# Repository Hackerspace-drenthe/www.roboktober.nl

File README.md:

# Roboktober Monorepo

Dit is de centrale repository voor Roboktober van Hackerspace Drenthe: de website en API, elektronica, robotfirmware, presentaties, 3D-printontwerpen en foto's.

Roboktober is een oktober-evenement rond combat robots, met focus op bouwen, leren en community.

## Status: editie 2026 afgerond

**Bevestigd door Rein op 5 november 2026:** Roboktober 2026 is afgerond en klaar. De website is al enkele maanden operationeel en stabiel. De elektronica v4 werkt en is akkoord.

Deze repository bewaart het resultaat: website, robotbouwinformatie, firmware, ontwerpen, presentaties en beeldmateriaal. Historische plannen, audits en revisies blijven beschikbaar, maar zijn geen open opleverlijst voor 2026. Ideeën voor uitbreiding horen bij eventuele volgende edities. Normaal beheer, back-ups en veiligheidscontroles blijven van toepassing; projectafronding is geen nieuwe verklaring dat iedere afzonderlijke test of ontwerpvariant is gevalideerd.

## Wallie: website, uitleg en oorspronkelijke code

**Wallies werk is een belangrijke basis en inspiratiebron voor de robotbesturing, het mini-robotchassis en de presentatie.** Bezoek zijn eigen website en GitHub voor de oorspronkelijke uitleg, projecten en actuele ontwikkelingen:

- **Website:** [wallieonline.nl](https://wallieonline.nl/)
- **Robotcontroller-uitleg:** [WORC Robot Controller (Nederlands)](https://wallieonline.nl/blogs/worc-robot-controller-nl.html)
- **GitHub-profiel en alle repositories:** [github.com/wallieonline](https://github.com/wallieonline)

### Repositories voor de besturing

| Repository van Wallie | Wat vind je daar? |
| --- | --- |
| [wallieonline/worc-robot-controller-esp32c3](https://github.com/wallieonline/worc-robot-controller-esp32c3) | Robotcontrollerfirmware voor de ESP32-C3 en DRV8833; bron voor de upstream referenties en codevoorbeelden in dit project. |
| [wallieonline/worc-remote-controller-esp32](https://github.com/wallieonline/worc-remote-controller-esp32) | ESP32-afstandsbediening: de zenderkant van de besturingsketen en bron voor de presentatievoorbeelden. |

De lokale Roboktober-firmware en eigen ontwerpen zijn niet hetzelfde als Wallies actuele upstream projecten. De bewaarde firmwarebron en herkomst staan onder [electronics/firmware/upstream](./electronics/firmware/upstream/). Raadpleeg de licentie en bronvermelding van het betreffende bestand bij gebruik of herpublicatie; deze repository verleent geen algemene rechten op Wallies werk.

## Projectdoelen

De doelen zijn uitgewerkt in het [projectplan](./docs/PLAN.md):

1. Mensen warm maken voor het event met teaser-content, planning en sfeer.
2. Deelnemers helpen bouwen met complete en praktische bouwinformatie.
3. Assets duurzaam beschikbaar houden, zoals BOM, STL, bouwdocs, blog en links.
4. Een herbruikbare basis neerzetten voor toekomstige Roboktober-edities.

## Context

- Eerste editie: 2026.
- Publieke domeinnaam: https://roboktober.nl.
- Website-taal: Nederlands.

## Repository-structuur

De repository combineert **robotbouw**, **software**, **presentaties** en **beeldmateriaal**. De belangrijkste mappen staan hieronder. Firmware is onderdeel van `electronics`; er is geen aparte firmwaremap in de root.

```text
.
├── electronics/                 Elektronica en robotfirmware
│   ├── components/             Onderdelen en selectiecriteria
│   ├── pin-definitions/        Pincontracten voor de modules
│   ├── wiring/                 Bedrading en bouwinstructies
│   ├── schema/                 Elektrische ontwerpkeuzes
│   ├── kicad/                  PCB-projecten en revisies
│   └── firmware/               Eigen firmware en upstream bronnen
├── 3dprinter/                  Chassis en 3D-printonderdelen
│   ├── Wallieonline+Mini+Robot+chassis/
│   └── reinsdesigns/           Eigen ontwerpen en varianten
├── presentaties/               Presentatiebronnen per editie en taal
├── fotos/                      Foto's en video per onderwerp
├── roboktober-api/             Website-backend en beheer
├── roboktober-frontend/        Publieke website
├── deploy/                    Server- en deploymentbestanden
└── docs/                      Plannen en verdiepende documentatie
```

Dit is een functioneel overzicht, geen volledige bestandslijst. Gebruik de links hieronder voor de inhoud en instructies per onderdeel.

### 1. Robotbouw: elektronica en firmware

[electronics](./electronics/README.md) bevat de informatie om de besturing van een antweight-robot op te bouwen: onderdelen, voedingskeuzes, pinnen, bedrading en PCB-ontwerpen. De controller draait rond een ESP32-C3 en een DRV8833-motordriver.

| Map | Inhoud en gebruik |
| --- | --- |
| [components](./electronics/components/) | Onderdelen/stuklijsten en selectiecriteria voor de elektronica. |
| [pin-definitions](./electronics/pin-definitions/) | Pincontracten en controlepunten: welke aansluiting hoort bij welke functie? |
| [wiring](./electronics/wiring/) | Bedradingsinstructies voor de bouw en het zoeken naar aansluitproblemen. |
| [schema](./electronics/schema/) | Elektrische ontwerpkeuzes en netspecificaties. |
| [kicad](./electronics/kicad/) | PCB-bronnen en revisies. Het [v4-project](./electronics/kicad/hsd-antweight-2s-v4/) is volgens de elektronica-handleiding het leidende ontwerp; oudere revisies zijn archiefreferenties. |
| [firmware](./electronics/firmware/) | Software die op de robotcontroller draait, met eigen firmware en bewaarde upstream bronnen. |

Binnen firmware vind je:

- [roboktober-controller-v2](./electronics/firmware/roboktober-controller-v2/README.md): de eigen controllerfirmware, inclusief hardwarecontract, zenderconfiguratie, motorbesturing, invoervalidatie, failsafe en compileerinstructies.
- [upstream](./electronics/firmware/upstream/): oorspronkelijke referentiecode met bijbehorende licentie, om herkomst en verschillen te kunnen volgen.

**Begin bij de elektronica-handleiding en controleer daarna het pincontract en de firmwareconfiguratie.** Een passend bestand of geslaagde compilatie is geen bewijs dat de fysieke robot veilig werkt. Test met de wielen vrij van de grond en controleer de uitschakeling bij verbindingsverlies.

### 2. Mechanica: chassis en 3D-printontwerpen

[3dprinter](./3dprinter/) bevat ontwerpbronnen en exports voor robotchassis en onderdelen. Een `.scad`-bestand is bewerkbare OpenSCAD-broncode; een `.stl` is een mesh voor onder andere de slicer. Er staan ook STEP-bestanden en afbeeldingen voor bepaalde ontwerpen.

- [Wallieonline+Mini+Robot+chassis](./3dprinter/Wallieonline+Mini+Robot+chassis/): Wallies mini-robotchassis en topplaat, met STL-bestanden en OpenSCAD-/STEP-varianten.
- [reinsdesigns](./3dprinter/reinsdesigns/): eigen ontwerpen en opeenvolgende varianten, waaronder Disc Spinner, Limulus, Passive Aggressive, Racer, Rhomboid en Mostly Harmless.
- [Print- en montagehandleiding](./3dprinter/README.md): schaaladvies en de beschreven passing van Wallies topplaat op de v4-PCB.

Versienummers in bestandsnamen maken ontwerpevolutie zichtbaar; ze betekenen niet automatisch dat elke variant is gebouwd of gevalideerd. Controleer vóór het printen de afmetingen, beschikbare onderdelen en de passing van jouw combinatie van chassis en elektronica.

### 3. Presentaties en uitleg

[presentaties](./presentaties/) bevat de presentatiebronnen per bijeenkomst en taal. Voor PHP Meetup Groningen op **5 november 2026** zijn er twee versies:

- [Nederlands](./presentaties/php-meetup-groningen-2026-11-05/slides/README.md)
- [Engels](./presentaties/php-meetup-groningen-2026-11-05-en/slides/README.md)

Elke versie heeft een `PLAN.md` en een `slides/`-map met de presentatie, stijlen, scripts, lokale afbeeldingen/video en speaker notes. De bijbehorende README beschrijft het openen en verpakken van de slides. De presentatie volgt de keten van joystick tot wiel en verbindt software, elektronica en chassisontwerp.

### 4. Foto's en video

[fotos](./fotos/) bewaart lokaal beeldmateriaal uit de bouw en het evenement:

| Map | Onderwerp |
| --- | --- |
| [controller](./fotos/controller/) | Controllers en besturing. |
| [mensenbezig](./fotos/mensenbezig/) | Deelnemers en bouwactiviteiten. |
| [robots](./fotos/robots/) | Gebouwde robots. |
| [video](./fotos/video/) | Videomateriaal. |

Presentaties hebben daarnaast hun eigen lokale slide-assets. Een bestand in deze repository betekent niet automatisch dat het vrij herpubliceerbaar is: behoud bronvermeldingen en controleer de toepasselijke rechten en toestemmingen.

### 5. Website, API en server

- [roboktober-api](./roboktober-api/README.md): Laravel-backend, API en Filament-beheer.
- [roboktober-frontend](./roboktober-frontend/README.md): Vue-frontend voor de publieke website.
- [deploy](./deploy/README.md): deploymentinstructies en configuratie voor Apache en systemd.

Deze onderdelen vormen het operationele webplatform, niet de robotfirmware. Architectuur, lokale ontwikkeling, Docker en deployment zijn uitgewerkt in [docs/SERVER.md](./docs/SERVER.md).

### 6. Plannen en projectdocumentatie

[docs](./docs/README.md) is de ingang naar de verdiepende documentatie:

- [PLAN.md](./docs/PLAN.md): functioneel en technisch masterplan.
- [PLAN-CHANGES.md](./docs/PLAN-CHANGES.md): aanvullingen en wijzigingen op het plan.
- [Architectuur](./docs/ARCHITECTUUR.md): platformarchitectuur.
- [Perspakket](./docs/pers/README.md): persinformatie en geselecteerd beeldmateriaal.
- [ADR's](./docs/adr/README.md) en [release notes](./docs/release-notes/README.md): vastgelegde keuzes en wijzigingshistoriek.

## Waar begin je?

| Je wilt… | Begin hier |
| --- | --- |
| Een robot bouwen of aansluiten | [Elektronica](./electronics/README.md), daarna [bedrading](./electronics/wiring/) en [firmware](./electronics/firmware/roboktober-controller-v2/README.md). |
| Een chassis kiezen, aanpassen of printen | [3D-printontwerpen](./3dprinter/) en de [printinstructies](./3dprinter/README.md). |
| De presentatie bekijken of voorbereiden | [Nederlandse](./presentaties/php-meetup-groningen-2026-11-05/slides/README.md) of [Engelse presentatie](./presentaties/php-meetup-groningen-2026-11-05-en/slides/README.md). |
| Beeldmateriaal zoeken | [Foto's en video](./fotos/); voor persgebruik het [perspakket](./docs/pers/README.md). |
| De website lokaal draaien of deployen | [Website en server](./docs/SERVER.md). |
| Scope, keuzes en projecthistoriek begrijpen | [Documentatie-index](./docs/README.md). |

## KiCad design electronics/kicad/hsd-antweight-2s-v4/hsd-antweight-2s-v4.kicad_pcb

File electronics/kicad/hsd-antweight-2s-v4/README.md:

# V4 print: module-based carrier board voor 1S LiPo default

Deze map bevat de v4-variant van de antweight-controllerprint. Het uitgangspunt is simpel:

- de PCB is de bron van waarheid
- de fysieke layout is gebaseerd op de bewezen v3-fix print
- de standaardopstelling is 1S LiPo
- de DRV8833 sleep/control pin zit op GPIO5
- 2S is alleen een expliciete optionele route, niet de default

## Projectstatus

Op 2026-11-05 heeft de gebruiker bevestigd dat de v4-elektronica werkt en
goedgekeurd is; het 2026-project is afgerond. Dit is geen nieuw testresultaat
of certificering en stelt niet vast dat elke optionele voedingsroute
afzonderlijk is getest.

## 1. Wat is de v4 in praktijk?

De v4 is geen volledig custom power-design. Het is een compacte carrier board voor bestaande modules:

- ESP32-C3 SuperMini
- DRV8833-breakout
- 1S LiPo charge/protection breakout
- motorconnectors
- testpoints en debug-headers

Het doel is om een praktische print te hebben die compact genoeg is voor een robot, zonder een ingewikkelde custom-voedingsarchitectuur te bouwen.

> Als een label, schema of document afwijkt van de PCB, dan geldt de PCB als de juiste referentie.

## 2. Standaardvoeding: 1S LiPo is de default

Voor deze robotbouw is de standaardconfiguratie:

- 1S LiPo batterij
- charge/protection breakout module
- output naar de PCB-power-rail
- ESP-logic en motor-power gescheiden houden

Dit betekent:

- de accu is een 1S-cel, ongeveer 3,7V tot 4,2V
- de ESP krijgt een veilige, gestabiliseerde 5V-rail via de module-route
- de motorstroom blijft apart van de ESP-logica
- de print is ontworpen voor de praktische standaardbouw, niet voor een complexe custom-power-variant

### 2.1 Waarom 1S als default?

- simpel
- compact
- veilig
- makkelijk te reproduceren
- het werkt het beste voor een kleine antweight-bouw met N20-motoren

### 2.2 Historische kostenindicatie: minimale 1S-kit

In de oorspronkelijke v4-planning werd een praktische richtprijs van ongeveer
EUR 25 voor een complete minimale 1S-kit per robot gehanteerd.

Dit is een historische inkoopindicatie, geen actuele offerte; de prijs kan
variëren door voorraad, leverancier, verzendkosten en batchgrootte.

### 2.3 Optionele 2S-route

Een 2S-configuratie kan als aparte route worden gebruikt, maar dat is bedoeld als alternatief en niet als standaardopstelling.

- 2S accu -> regulator -> ESP_5V_IN
- deze route moet expliciet worden gekozen en gecontroleerd
- meer vermogen, maar ook meer stroom, meer warmte en meer aandacht nodig

## 3. Belangrijkste elektrische afspraken

### DRV8833 sleep/control

GPIO5 is de sleep/control pin voor de DRV8833 in deze configuratie.

- niet zomaar vervangen door een willekeurige GPIO
- deze pin is onderdeel van de bedoeling van de print
- als je firmware of schema hier vanaf wijkt, dan is de PCB de bron van waarheid

### Power rails

Op deze print gelden deze afspraken:

- VBAT_RAW: ruwe batterijspanning
- VBAT_SW: geschakelde / gebruikelijke batterijrail
- ESP_5V_IN: 5V-ingang voor de ESP
- REG_5V_OUT: 5V-uitgang van een optionele regulator/route
- GND: massa

### Default path

De standaard route is:

- 1S LiPo charge/protection breakout -> VBAT_SW / ESP_5V_IN
- motor-power en ESP-power gescheiden houden
- 2S route aparte en optioneel

## 4. Eerste opstart: veilig en eenvoudig

### Stap 1: controleer de print

- controleer op beschadigde sporen of pads
- controleer de batterijconnector
- controleer de jumper/route voor je gekozen voeding

### Stap 2: kies je voeding

Gebruik deze eenvoudige regel:

- beginner / standaard: 1S-setup
- wedstrijd / speciale build: 2S optioneel via juiste regulator-route

Als je niet zeker bent, begin met de standaard 1S-opstelling.

### Stap 3: sluit de batterij aan

- zet de stroom uit voordat je iets aansluit
- sluit de batterij met juiste polariteit aan
- controleer GND en batterijpoles nogmaals

### Stap 4: sluit de motoren aan

- linker motor op linker connector
- rechter motor op rechter connector
- controleer of de pinning klopt

### Stap 5: zet de print aan

- controleer dat de ESP opstart
- controleer status en gedrag
- test zonder extra belasting eerst

## 5. Testen met USB-5V

Je kunt de ESP ook testen zonder de accu aan te sluiten door de print via USB-5V te voeden.

### Praktische regel

Gebruik altijd deze volgorde:

1. zet de batterij los
2. voer de print alleen via USB-5V
3. test de ESP en firmware
4. sluit daarna pas de accu weer aan voor een volledige batterijtest

### Belangrijk

Als USB-5V en accu tegelijk aanwezig zijn, kunnen beide voedingen op dezelfde print samenkomen. Dat is niet automatisch fataal, maar het kan leiden tot ongewenste backfeeding of onduidelijk gedrag.

Voor een veilige eerste test: batterij loskoppelen, dan USB-5V gebruiken, daarna pas opnieuw met accu testen.

## 6. Veilige bedradingsregels

- geen raw batterij direct op de 3.3V-rail van de ESP
- geen motor rechtstreeks op een ESP-pin
- alleen voeding op de daarvoor bestemde power-rails
- GND goed aansluiten tussen batterij, ESP en driver
- GPIO5 niet verwarren met een algemene vrije GPIO

## 7. Snelle technische samenvatting

- ESP-voeding: ESP_5V_IN
- standaard default: 1S LiPo
- optioneel alternatief: 2S via regulator route
- motorsturing: DRV8833
- sleep/control: GPIO5
- common ground: GND

## 8. Projectbestanden

- PCB: hsd-antweight-2s-v4.kicad_pcb
- Schema: hsd-antweight-2s-v4.kicad_sch
- Project: hsd-antweight-2s-v4.kicad_pro
- renders: renders/

## 9. Belangrijkste opmerking

Deze print is de werkelijke bron van waarheid. De v4 is een compacte
carrier-board-variant op basis van de v3-fix-layout, met 1S LiPo als standaard
en GPIO5 als DRV8833 sleep/control line. De oorspronkelijke beschrijving noemt
de v3-fix-layout bewezen; dit document voegt daar geen nieuwe fysieke
testresultaten aan toe.

De eerder vastgelegde DRC-controle van de PCB rapporteerde 0 violations en
0 unconnected items. Dit is het bestaande resultaat, geen nieuwe DRC-run.

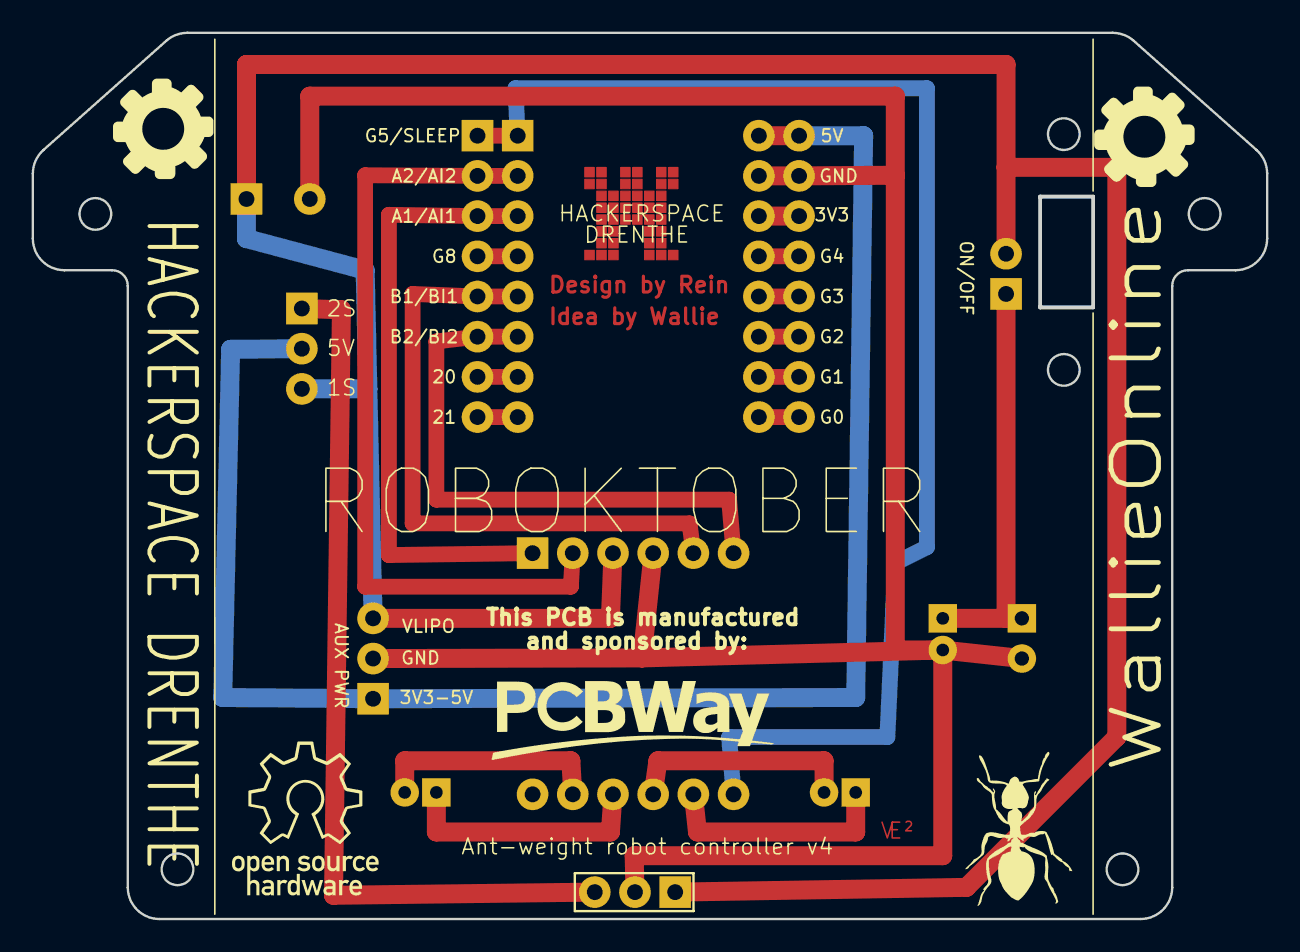
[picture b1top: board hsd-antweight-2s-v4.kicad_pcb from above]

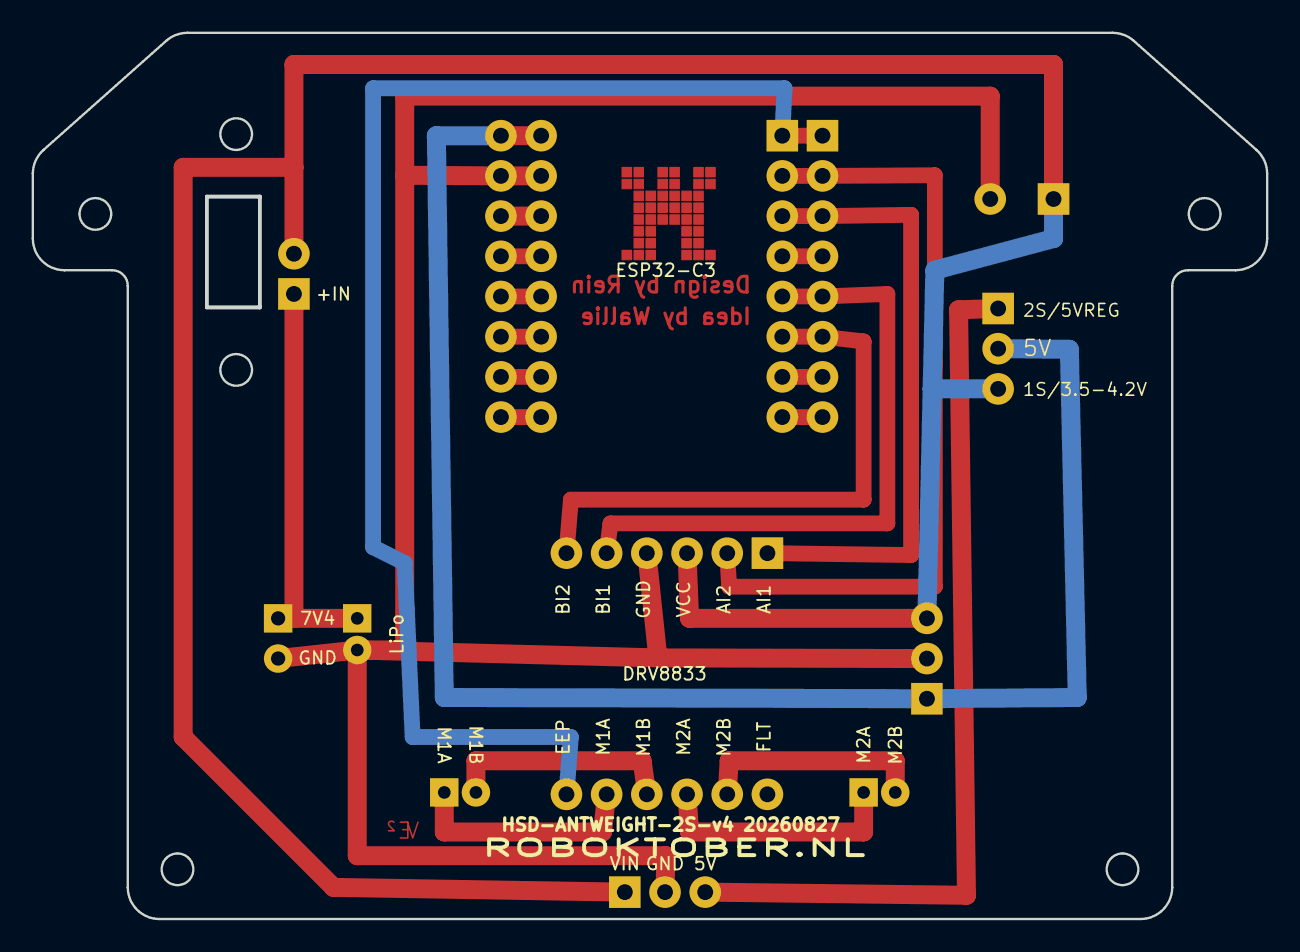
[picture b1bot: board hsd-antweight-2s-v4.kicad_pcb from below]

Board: 2 copper layers, 78.0 x 56.0 mm, 11 parts (10 on the bottom side), 14 nets.

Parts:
C1_C2: DRIVER CAPS; CAPS_DRIVER
J4: BATTERY; JST_PH_BATTERY
J4_ALT: BATTERY_ALT_2P_2.54; PinHeader_1x02_P2.54mm_Vertical
J5: MOTOR LEFT; JST_PH_MOTOR
J6: MOTOR RIGHT; JST_PH_MOTOR
J10: 5V(3.7-5V) GND VLIPO; ACCESSORY_POWER_1X03_UNPOPULATED
JP1: ESP 5V SEL: REG-ESP; ACCESSORY_POWER_1X03_UNPOPULATED
SW1: SW EXT VBAT_RAW/VBAT_SW; SWITCH_EXT_1X02
U1: ESP32-C3 SUPERMINI; ESP32_C3_SUPERMINI
U2: DRV8833; DRV8833_MACHINED_SOCKET_VERIFY
U3: EXT REG LOGIC VIN GND VOUT; REGULATOR_EXT_1X03

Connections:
AIN1_GPIO7: U1.3, U2.1
AIN2_GPIO6: U1.2, U2.3
BIN1_GPIO9: U1.5, U2.9
BIN2_GPIO10: U1.6, U2.11
ESP_5V_IN: J10.1, JP1.2, U1.16
GND: C1_C2.2, J4.2, J4_ALT.2, J10.2, U1.15, U2.7, U3.2
GPIO5: U1.1, U2.12
M1A: J5.1, U2.10
M1B: J5.2, U2.8
M2A: J6.1, U2.6
M2B: J6.2, U2.4
REG_5V_OUT: JP1.1, U3.3
VBAT_RAW: J4.1, J4_ALT.1, SW1.1
VBAT_SW: C1_C2.1, J10.3, JP1.3, SW1.2, U2.5, U3.1

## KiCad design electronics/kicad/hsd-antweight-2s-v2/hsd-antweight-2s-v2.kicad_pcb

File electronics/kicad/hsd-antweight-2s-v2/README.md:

# KiCad antweight controller v2 - hsd-antweight-2s-v2

This KiCad 9 project is the current 2S-oriented board variant with
externalized power interfaces.

Current board silk details:

- logo area: `HACKERSPACE` above `DRENTHE`
- J10 pad 3 raw rail silk: `VLIPO` (electrically `VBAT_SW`)

Power-mode placement update (component-only, routing deferred):

- Added `JP1` (`ESP PWR SEL: REG-3V3-1S`) near `U3`.
- `JP1` maps: `1=REG_3V3_2S`, `2=ESP_3V3`, `3=VBAT_SW`.
- 2S mode: place `U3`, shunt `JP1` pins `1-2`.
- 1S mode: do not place `U3` (DNP), shunt `JP1` pins `2-3`.
- Motor driver path still uses `VBAT_SW` directly in both modes.
- This revision intentionally focuses on component placement only; routing will be redone later.

## Status

The schematic is documented and the PCB is now proto-ready for
PCBWay 2-layer fabrication.

This folder diverges from the archived legacy board layout by externalizing
the power path:

- `SW1` is a 2-pin external switch header (`VBAT_RAW` <-> `VBAT_SW`).
- Bypass mode uses a 2-pin shunt directly on `SW1`.
- `U3` is a 3-pin external regulator header
  (`VIN`, `GND`, `VOUT=3V3`).

Use this revision for prototype fabrication only.
It is not yet a locked mass-production release.

## Validation

```bash
kicad-cli sch erc --severity-error \
  electronics/kicad/hsd-antweight-2s-v2/hsd-antweight-2s-v2.kicad_sch
kicad-cli sch export netlist \
  electronics/kicad/hsd-antweight-2s-v2/hsd-antweight-2s-v2.sch
kicad-cli pcb drc \
  electronics/kicad/hsd-antweight-2s-v2/hsd-antweight-2s-v2.kicad_pcb \
  --severity-all
```

Latest validation snapshot (2026-08-12):

- ERC errors: 0 (`--severity-error` gate passes)
- DRC violations: 0
- Unconnected pads: 0
- Footprint errors: 0
- Full ERC warning report still contains expected legacy wiring warnings.

Before manufacturing review:

- convert the schematic fully to native KiCad format;
- replace all `*_VERIFY` footprints with production footprints;
- rerun ERC and DRC after every electrical/layout change;
- inspect antenna clearance and high-current routes.

## PCBWay proto package

Generated package root:

- `production/pcbway/`

Upload-ready archive:

- `production/pcbway/hsd-antweight-2s-v2-pcbway-proto-package-2026-08-12.zip`

Contents:

- `gerbers/`: copper, mask, silkscreen and edge cuts Gerbers
- `drill/`: PTH/NPTH drill files, maps and drill report
- `hsd-antweight-2s-v2-pos.csv`: placement file
- `hsd-antweight-2s-v2-bom.csv`: BOM export
- `hsd-antweight-2s-v2.net`: KiCad netlist export

## 3D render (current revision)

Render images are stored in `renders/`.
All renders in this folder are PCB-only (no external connectors, modules or capacitors).

Primary preview (top overview, PCB-only):

Generated artifacts (6 views):

- Top:
  - `renders/pcbway-bare-top-1-overview.png`
  - `renders/pcbway-bare-top-2-angle-left.png`
  - `renders/pcbway-bare-top-3-angle-right.png`
- Bottom:
  - `renders/pcbway-bare-bottom-1-overview.png`
  - `renders/pcbway-bare-bottom-2-angle-left.png`
  - `renders/pcbway-bare-bottom-3-angle-right.png`

Render command:

Settings below are tuned so the complete PCB (including holes, pads,
traces and vias) stays visible in frame.

```bash
PCB="electronics/kicad/hsd-antweight-2s-v2/hsd-antweight-2s-v2.kicad_pcb"
TMP="electronics/kicad/hsd-antweight-2s-v2/hsd-antweight-2s-v2-no-3dmodels.tmp.kicad_pcb"

perl -ne '
sub balance { my ($s)=@_; my $o=()=$s=~/\(/g; my $c=()=$s=~/\)/g; return $o-$c; }
if (!$skip && /\(model\s+/) { $skip=1; $depth=balance($_); next; }
if ($skip) { $depth += balance($_); if ($depth <= 0) { $skip=0; } next; }
print;
' "$PCB" > "$TMP"

kicad-cli pcb render \
  --width 3200 \
  --height 2400 \
  --background transparent \
  --quality high \
  --zoom 1.00 \
  --rotate "0,0,0" \
  --side top \
  --output \
  electronics/kicad/hsd-antweight-2s-v2/renders/pcbway-bare-top-1-overview.png \
  "$TMP"

kicad-cli pcb render \
  --width 3200 \
  --height 2400 \
  --background transparent \
  --quality high \
  --perspective \
  --zoom 1.04 \
  --rotate "-20,0,18" \
  --side top \
  --output \
  electronics/kicad/hsd-antweight-2s-v2/renders/pcbway-bare-top-2-angle-left.png \
  "$TMP"

kicad-cli pcb render \
  --width 3200 \
  --height 2400 \
  --background transparent \
  --quality high \
  --perspective \
  --zoom 1.04 \
  --rotate "20,0,-18" \
  --side top \
  --output \
  electronics/kicad/hsd-antweight-2s-v2/renders/pcbway-bare-top-3-angle-right.png \
  "$TMP"

rm -f "$TMP"
```

Render bottom views (PCB-only):

```bash
PCB="electronics/kicad/hsd-antweight-2s-v2/hsd-antweight-2s-v2.kicad_pcb"
TMP="electronics/kicad/hsd-antweight-2s-v2/hsd-antweight-2s-v2-no-3dmodels.tmp.kicad_pcb"

perl -ne '
sub balance { my ($s)=@_; my $o=()=$s=~/\(/g; my $c=()=$s=~/\)/g; return $o-$c; }
if (!$skip && /\(model\s+/) { $skip=1; $depth=balance($_); next; }
if ($skip) { $depth += balance($_); if ($depth <= 0) { $skip=0; } next; }
print;
' "$PCB" > "$TMP"

kicad-cli pcb render \
  --width 3200 \
  --height 2400 \
  --background transparent \
  --quality high \
  --zoom 1.00 \
  --rotate "0,0,0" \
  --side bottom \
  --output \
  electronics/kicad/hsd-antweight-2s-v2/renders/pcbway-bare-bottom-1-overview.png \
  "$TMP"

kicad-cli pcb render \
  --width 3200 \
  --height 2400 \
  --background transparent \
  --quality high \
  --perspective \
  --zoom 1.04 \
  --rotate "-20,0,18" \
  --side bottom \
  --output \
  electronics/kicad/hsd-antweight-2s-v2/renders/pcbway-bare-bottom-2-angle-left.png \
  "$TMP"

kicad-cli pcb render \
  --width 3200 \
  --height 2400 \
  --background transparent \
  --quality high \
  --perspective \
  --zoom 1.04 \
  --rotate "20,0,-18" \
  --side bottom \
  --output \
  electronics/kicad/hsd-antweight-2s-v2/renders/pcbway-bare-bottom-3-angle-right.png \
  "$TMP"

rm -f "$TMP"
```

## Release checklist

- [ ] `*_VERIFY` footprints replaced by production footprints.
- [ ] Mounting-hole implementation and coordinates verified.
- [ ] Current ratings validated for switch and connectors.
- [x] ERC and DRC rerun and reports archived.
- [ ] Final visual review completed.

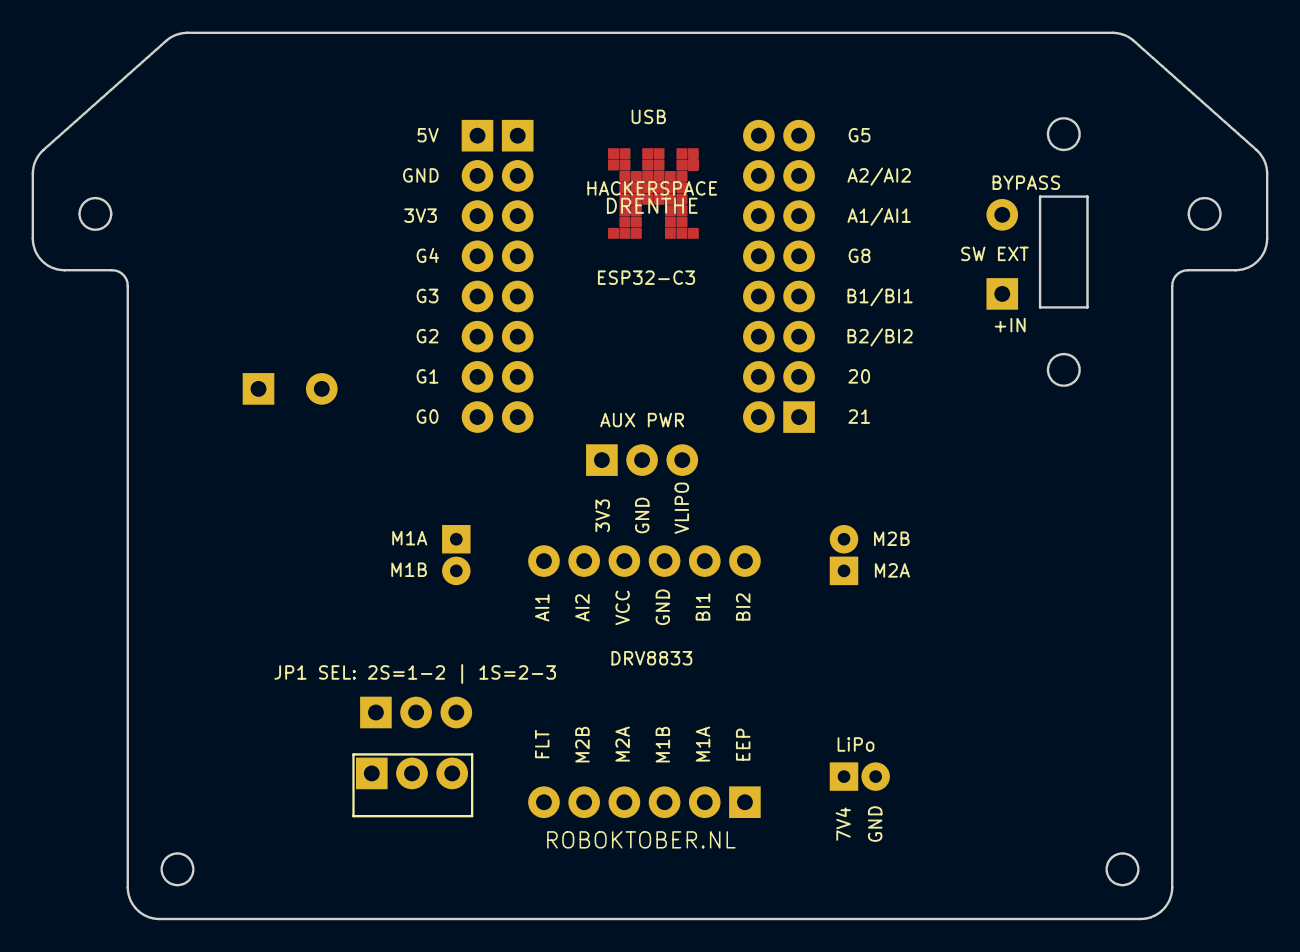
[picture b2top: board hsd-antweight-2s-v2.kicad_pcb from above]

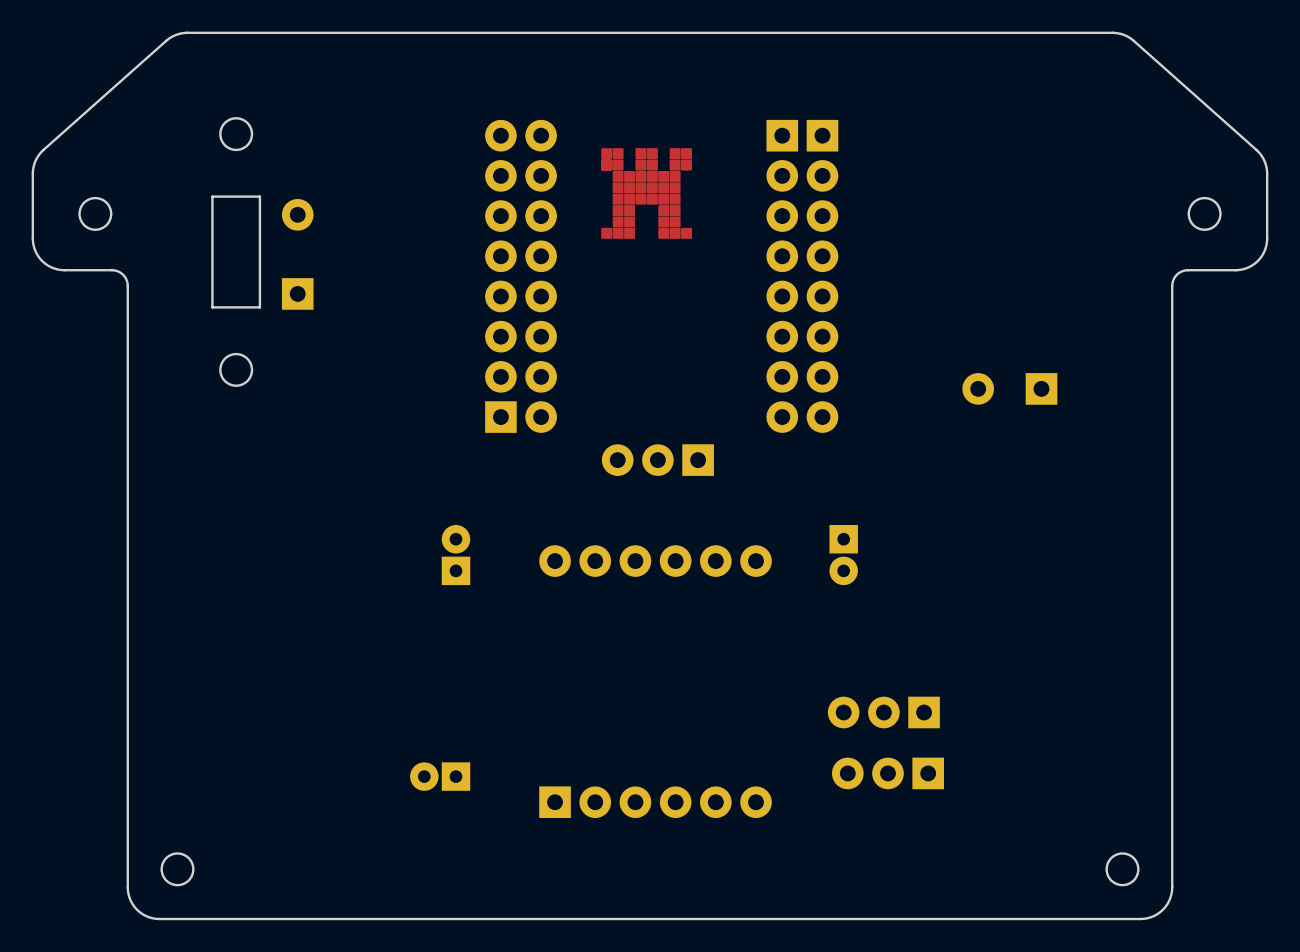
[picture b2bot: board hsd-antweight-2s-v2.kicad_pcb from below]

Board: 2 copper layers, 78.0 x 56.0 mm, 12 parts (11 on the bottom side), 23 nets, no tracks yet.

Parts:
C1_C2: DRIVER CAPS; CAPS_DRIVER
J4: BATTERY; JST_PH_BATTERY
J5: MOTOR LEFT; JST_PH_MOTOR
J6: MOTOR RIGHT; JST_PH_MOTOR
J8: ESP32 LEFT ALL PINS; ESP32_LEFT_ALL_PINS_BREAKOUT_1X08_UNPOPULATED
J9: ESP32 RIGHT SIGNALS; ESP32_RIGHT_SIGNAL_BREAKOUT_1X08_UNPOPULATED
J10: 3V3 GND VLIPO; ACCESSORY_POWER_1X03_UNPOPULATED
JP1: ESP PWR SEL: REG-3V3-1S; ACCESSORY_POWER_1X03_UNPOPULATED
SW1: SW EXT VBAT_RAW/VBAT_SW; SWITCH_EXT_1X02
U1: ESP32-C3 SUPERMINI; ESP32_C3_SUPERMINI
U2: DRV8833; DRV8833_MACHINED_SOCKET_VERIFY
U3: EXT REG LOGIC VIN GND VOUT; REGULATOR_EXT_1X03

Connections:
3V3: J8.3, J10.1, JP1.2, U1.3
5V_NC: J8.1, U1.1
AIN1_GPIO7: J9.3, U1.11, U2.11
AIN2_GPIO6: J9.2, U1.10, U2.9
BIN1_GPIO9: J9.5, U1.13, U2.3
BIN2_GPIO10: J9.6, U1.14, U2.1
GND: C1_C2.2, J4.2, J8.2, J10.2, U1.2, U2.2, U2.5, U3.2
GPIO0_SPARE: J8.8, U1.8
GPIO1_SPARE: J8.7, U1.7
GPIO2_SPARE: J8.6, U1.6
GPIO3_SPARE: J8.5, U1.5
GPIO4_SPARE: J8.4, U1.4
GPIO5_SPARE: J9.1, U1.9
GPIO8_LED_EXPANSION: J9.4, U1.12
GPIO20_SPARE: J9.7, U1.15
GPIO21_SPARE: J9.8, U1.16
M1A: J5.1, U2.4
M1B: J5.2, U2.6
M2A: J6.1, U2.8
M2B: J6.2, U2.10
REG_3V3_2S: JP1.1, U3.3
VBAT_RAW: J4.1, SW1.1
VBAT_SW: C1_C2.1, J10.3, JP1.3, SW1.2, U2.7, U3.1

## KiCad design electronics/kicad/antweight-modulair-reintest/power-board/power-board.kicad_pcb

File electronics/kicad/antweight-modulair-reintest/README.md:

# Antweight modulair reintest

Dit ontwerp splitst de huidige controller op in twee stapelbare boards:

- `power-board/`: onderste board, met alleen power-conversie en power-distributie.
- `cpu-board/`: middelste board, met ESP32-C3, DRV8833, motorconnectoren en addon-header.

Een optionele derde board kan later als experiment/addon bovenop de CPU-board komen.

## Board split

CPU board verantwoordelijkheden:
- ESP32-C3 module/sockets
- DRV8833 driver
- motorconnectoren
- lokale driver-ontkoppeling
- stack-header naar power board
- addon-header voor spare GPIO en logic power
- logische netnamen voor motorbesturing

Power board verantwoordelijkheden:
- 2S LiPo ingang
- hoofdschakelaar
- buck 6V voor motoren
- buck 3.5V voor CPU-board
- stack-header omhoog naar CPU/DRV-board
- optionele aux power header

## Belangrijke nets

- `VBAT_2S_RAW`: ruwe 2S LiPo
- `VBAT_2S_SW`: geschakelde 2S LiPo
- `VMOTOR_6V`: gereguleerde motorvoeding
- `VCPU_3V5`: gereguleerde CPU-voeding
- `GND`
- `AIN1_GPIO7`, `AIN2_GPIO6`, `BIN1_GPIO9`, `BIN2_GPIO10`
- `M1A`, `M1B`, `M2A`, `M2B`
- `GPIO8_LED_EXPANSION`, `GPIO5_SPARE`

## Stack order

1. `power-board` onderaan
2. `cpu-board` in het midden
3. optionele addon/experiment board bovenop de CPU-board

De stack-header tussen power-board en CPU-board draagt alleen voedingsrails. Daardoor kan de power-board in theorie door een andere variant worden vervangen, bijvoorbeeld een 1S power-board, zonder DRV8833 of CPU-board te wisselen.

## Opmerking

De CPU-rail is hier expliciet als `VCPU_3V5` vastgelegd omdat dat gevraagd is. Controleer vóór hardwarebouw of de gekozen ESP32-C3 module direct 3.5V op zijn voedingspin mag hebben. Als dat niet kan, zet deze rail terug naar 3.3V in zowel schema als layout.

## Files

- `cpu-board/cpu-board.sch`: legacy schema bron voor CPU board
- `cpu-board/cpu-board.net`: geëxporteerde netlist
- `cpu-board/cpu-board.kicad_pcb`: eerste PCB met ESP32/DRV/motor-footprints
- `power-board/power-board.sch`: legacy schema bron voor power board
- `power-board/power-board.net`: geëxporteerde netlist
- `power-board/power-board.kicad_pcb`: eerste PCB met alleen power-footprints
- `stack-header-pinout.md`: interconnect pinout tussen beide boards

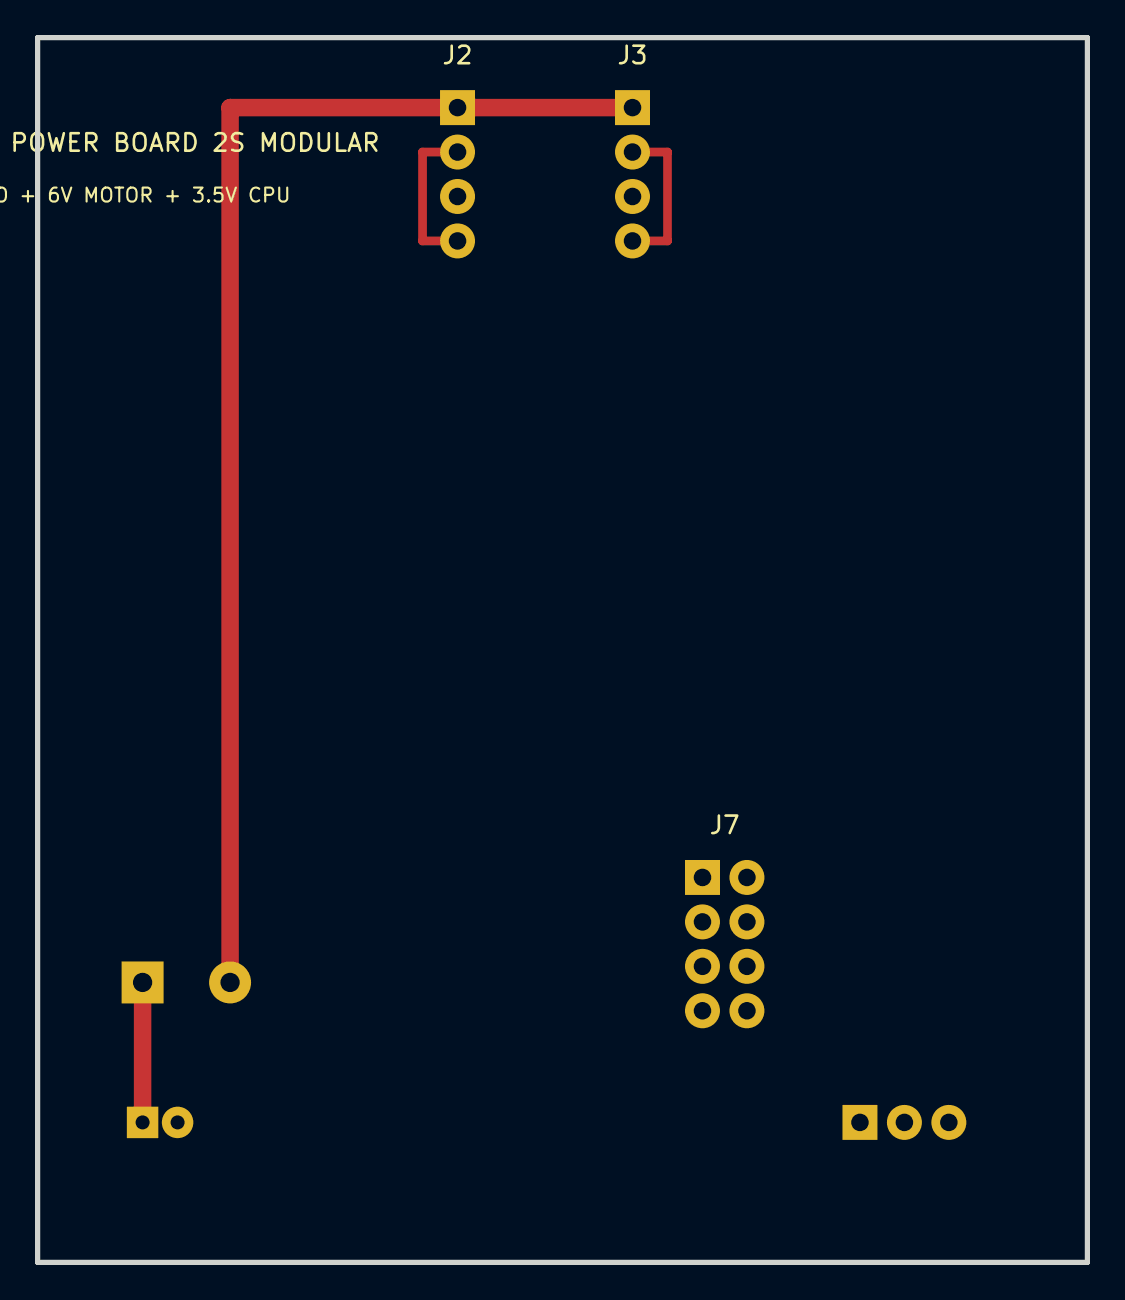
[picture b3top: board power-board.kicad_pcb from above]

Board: 2 copper layers, 60.0 x 70.0 mm, 6 parts (0 on the bottom side), 5 nets.

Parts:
J1: BATTERY_2S; JST_PH_BATTERY
J2: BUCK_6V_MOTOR; BUCK_HEADER_1X04
J3: BUCK_3V5_CPU; BUCK_HEADER_1X04
J7: STACK_TO_CPU_DRV; STACK_HEADER_2X04
J8: AUX_POWER; ACCESSORY_POWER_1X03_UNPOPULATED
SW1: MAIN_POWER; SWITCH_VERIFY

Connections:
GND: J1.2, J2.2, J2.4, J3.2, J3.4, J7.2, J7.4, J7.6, J7.8, J8.2
VBAT_2S_RAW: J1.1, SW1.1
VBAT_2S_SW: J2.1, J3.1, SW1.2
VCPU_3V5: J3.3, J7.1, J7.5, J8.1
VMOTOR_6V: J2.3, J7.3, J7.7, J8.3

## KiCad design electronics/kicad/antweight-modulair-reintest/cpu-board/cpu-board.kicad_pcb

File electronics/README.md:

# Roboktober electronics resources

Deze map bevat de gedeelde elektronica-informatie voor de Roboktober
antweight-builds.

## Inhoud

- `components/`: stuklijst en selectiecriteria voor onderdelen.
- `firmware/`: upstream referenties en de gereviewde Roboktober-firmware.
- `pin-definitions/`: logisch pincontract en controlepunten voor modules.
- `wiring/`: bedradingsinstructies voor bouw en foutzoeken.
- `schema/`: elektrische ontwerpkeuzes en netspecificatie.
- `kicad/antweight-controller-v2/`: historische legacy KiCad-projectmap
  (gearchiveerd).
- `kicad/hsd-antweight-2s-v4/`: leidend ontwerp voor de huidige
  ESP32-C3 controller revisie.
- `kicad/hsd-antweight-2s-v3-fix/`: historische tussenrevisie (archief).

Het leidende actieve ontwerp in deze repository is nu:

- v4 PCB: `kicad/hsd-antweight-2s-v4/`
- v4 power rule: minimale 1S setup is de standaard; 2S via regulator is optioneel
- v4 design notes: `docs/WALLIE-DESIGN-ISSUES.md`
- historische inkoopindicatie complete 1S-kit: ongeveer EUR 25 per robot

## Projectstatus

Op 2026-11-05 heeft de gebruiker bevestigd dat de v4-elektronica werkt en
goedgekeurd is; het 2026-project is afgerond. Dit is een brede
gebruikersbevestiging, geen nieuw testresultaat, certificering of verklaring
dat elke optionele voedingsconfiguratie afzonderlijk is getest.

De PCB in `kicad/hsd-antweight-2s-v4/` is de bron van waarheid voor het actuele ontwerp.
Legacy 3.3V-only en oudere 2S-documenten blijven alleen als archiefreferentie
bestaan voor vergelijking; ze zijn niet meer leidend voor bouw-, validatie- of
release-werk.

Publicatiestatus:

- De actieve v4-elektronica is door de gebruiker goedgekeurd zoals hierboven
  beschreven; er staat geen 2026 go/no-go- of prototypebesluit meer open.
- Die goedkeuring is geen certificering of bewijs van massaproductiegeschiktheid.
- Eerdere projectnotities beschreven de v4-print als proto-ready voor
  proefseries en hielden massaproductie tegen totdat footprints en thermische
  validatie definitief waren. Dat is een historische statusnotitie, geen
  openstaand projectbesluit; de huidige gebruikersbevestiging beweert niet dat
  die voorwaarden later zijn afgerond of dat massaproductie is vrijgegeven.
- De eerder genoemde circa EUR 25 per complete 1S-kit is een historische
  inkoopindicatie, geen actuele offerte.

## Reference design

Het leidende actieve ontwerp is de v4 revisie in `kicad/hsd-antweight-2s-v4/`.

Belangrijkste actuele regels:

- ESP32-C3 SuperMini voedt via `ESP_5V_IN`, niet via een legacy 3.3V-only rail;
- de module maakt intern 3.3V zelf; geen raw batterij op de ESP 3.3V pin;
- standaard route: minimale 1S setup via charge/protection breakout op de v4;
- optionele route: `2S -> 5V-regelaar -> ESP_5V_IN`;
- `VIN -> VOUT` bypass naar de ESP 3.3V rail blijft verboden;
- de v4 PCB en schematic zijn de bron van waarheid, niet de legacy 2S docs.

De oudere 2S/3.3V-only documenten in deze map blijven alleen als historische referentie
bestaan en mogen niet meer als actieve power-contract gelden.

Zie `docs/WALLIE-DESIGN-ISSUES.md` voor de definitieve design rules en
`kicad/hsd-antweight-2s-v4/README.md` voor de actuele PCB mapping.

## KiCad

Ontwerpstatus:

- v4 is het leidende ontwerp voor nieuwe hardware en validatie.
- De PCB en het schema in `kicad/hsd-antweight-2s-v4/` zijn de source-of-truth.
- Legacy ontwerpen in `kicad/hsd-antweight-2s-pcb/` en oudere mappen zijn archief.

Open `kicad/hsd-antweight-2s-v4/hsd-antweight-2s-v4.kicad_pro` met KiCad 9 of nieuwer.

Controleer bij een nieuwe revisie of onafhankelijke herhaling de actuele
power-path aan de hand van de PCB en het pincontract.

Voer voor een nieuwe revisie of onafhankelijke release-validatie minimaal uit:

```bash
kicad-cli sch erc --severity-error \
  kicad/hsd-antweight-2s-v4/hsd-antweight-2s-v4.kicad_sch
kicad-cli pcb drc kicad/hsd-antweight-2s-v4/hsd-antweight-2s-v4.kicad_pcb
```

Het ontwerp is geen gecertificeerd product. De bevestiging van de gebruiker
hierboven verandert dat niet. Test bij een nieuwe bouw eerst met een
stroombegrensde voeding en zonder gemonteerde motoren.

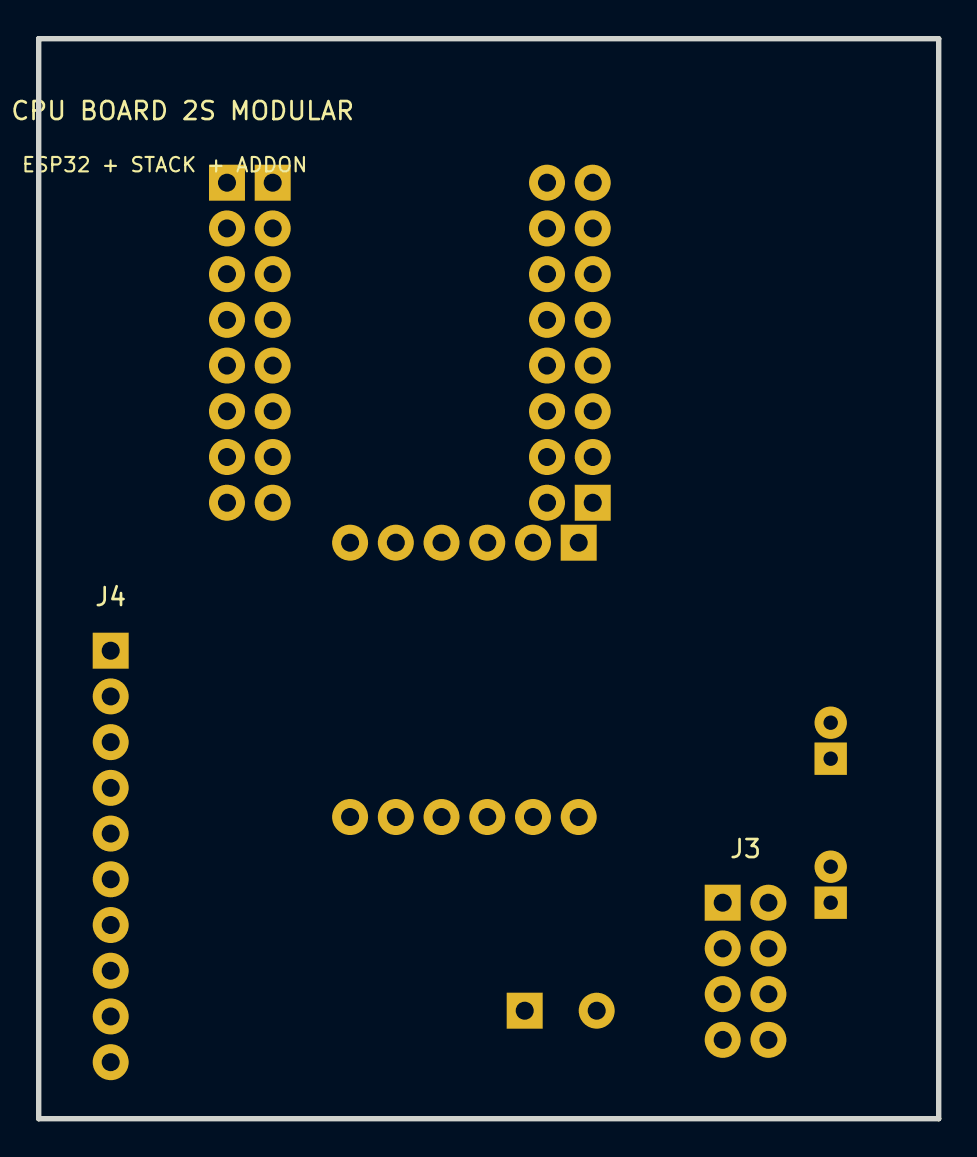
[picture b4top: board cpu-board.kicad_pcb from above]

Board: 2 copper layers, 50.0 x 60.0 mm, 9 parts (0 on the bottom side), 21 nets, no tracks yet.

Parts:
C1_C2: DRIVER CAPS; CAPS_DRIVER
J1: ESP32-C3_LEFT; ESP32_LEFT_ALL_PINS_BREAKOUT_1X08_UNPOPULATED
J2: ESP32-C3_RIGHT; ESP32_RIGHT_SIGNAL_BREAKOUT_1X08_UNPOPULATED
J3: STACK_TO_POWER; STACK_HEADER_2X04
J4: ADDON_HEADER; ADDON_HEADER_1X10
J5: MOTOR_LEFT; JST_PH_MOTOR
J6: MOTOR_RIGHT; JST_PH_MOTOR
U1: ESP32-C3 SUPERMINI; ESP32_C3_MACHINED_SOCKET_VERIFY
U2: DRV8833_BREAKOUT; DRV8833_MACHINED_SOCKET_VERIFY

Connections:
5V_NC: J1.1, U1.1
AIN1_GPIO7: J2.6, U1.14, U2.11
AIN2_GPIO6: J2.7, U1.15, U2.9
BIN1_GPIO9: J2.4, U1.12, U2.3
BIN2_GPIO10: J2.3, U1.11, U2.1
GND: C1_C2.2, J1.2, J3.2, J3.4, J3.6, J3.8, J4.2, U1.2, U2.2, U2.5
GPIO0_SPARE: J1.8, J4.3, U1.8
GPIO1_SPARE: J1.7, J4.4, U1.7
GPIO2_SPARE: J1.6, J4.5, U1.6
GPIO3_SPARE: J1.5, J4.6, U1.5
GPIO4_SPARE: J1.4, J4.7, U1.4
GPIO5_SPARE: J2.8, U1.16
GPIO8_LED_EXPANSION: J2.5, J4.10, U1.13
GPIO20_SPARE: J2.2, J4.8, U1.10
GPIO21_SPARE: J2.1, J4.9, U1.9
M1A: J5.1, U2.4
M1B: J5.2, U2.6
M2A: J6.1, U2.8
M2B: J6.2, U2.10
VCPU_3V5: J1.3, J3.1, J3.5, J4.1, U1.3
VMOTOR_6V: C1_C2.1, J3.3, J3.7, U2.7
